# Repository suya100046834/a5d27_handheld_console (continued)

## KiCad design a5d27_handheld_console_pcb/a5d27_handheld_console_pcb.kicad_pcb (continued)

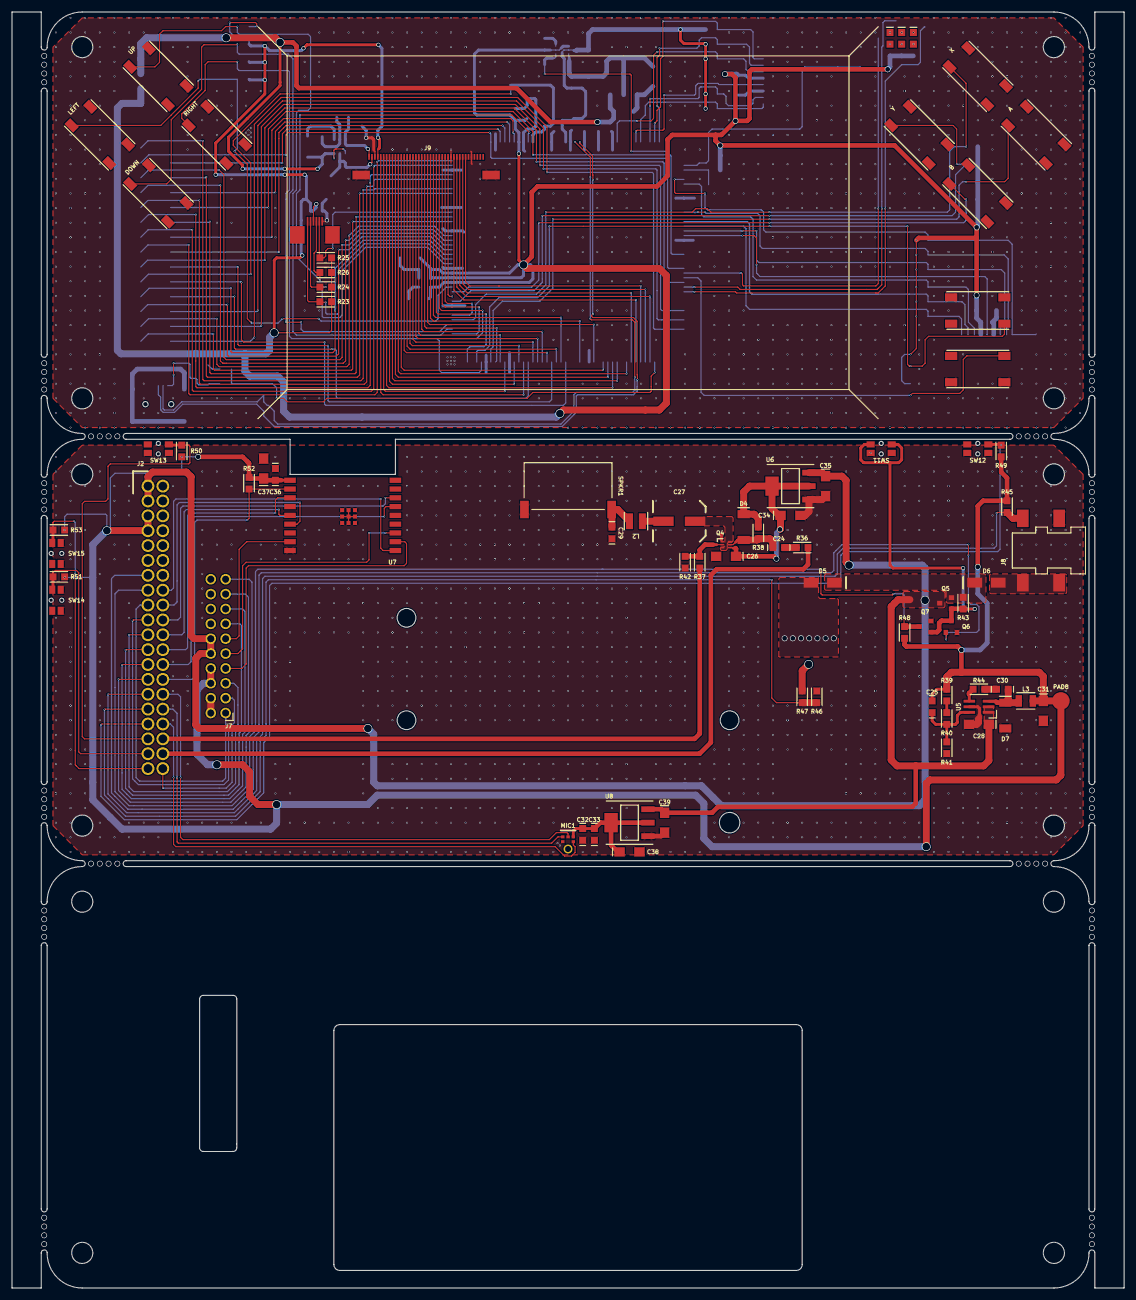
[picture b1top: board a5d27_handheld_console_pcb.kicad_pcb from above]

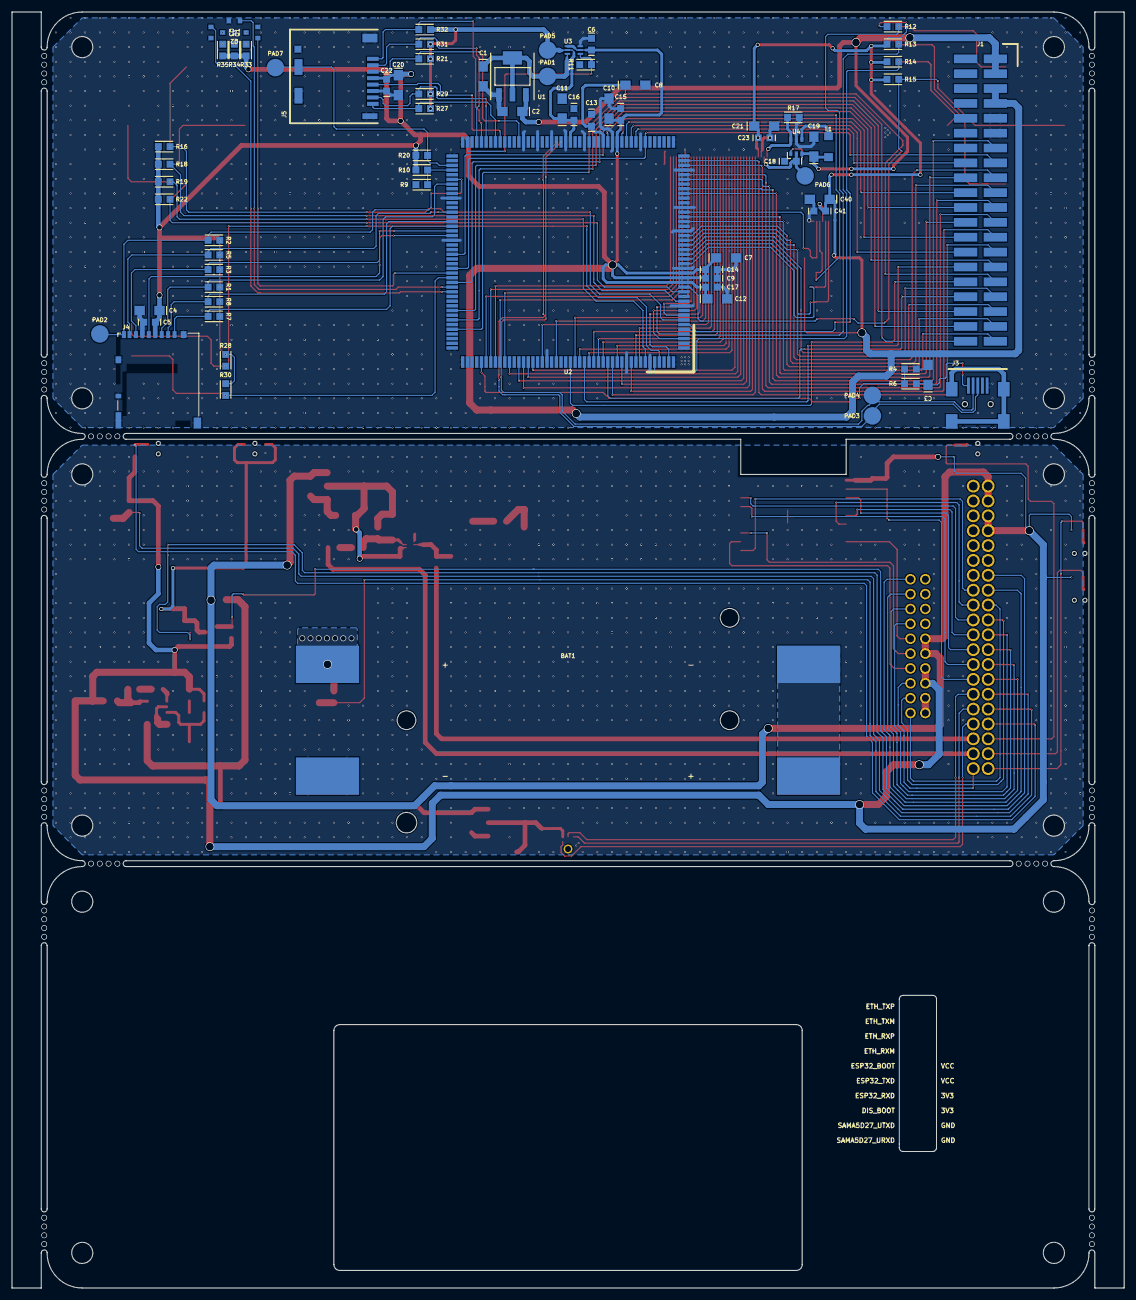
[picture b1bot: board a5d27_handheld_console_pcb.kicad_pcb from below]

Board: 2 copper layers, 190.0 x 218.0 mm, 153 parts (76 on the bottom side), 158 nets.

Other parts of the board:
A: A; SWITCH
B: B; SWITCH
DOWN: DOWN; SWITCH
LEFT: LEFT; SWITCH
RIGHT: RIGHT; SWITCH
UP: UP; SWITCH
X: X; SWITCH
Y: Y; SWITCH

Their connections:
/1_BOARD/BTN_1: UP.2; also elsewhere on the board
/1_BOARD/BTN_2: DOWN.2; also elsewhere on the board
/1_BOARD/BTN_3: RIGHT.2; also elsewhere on the board
/1_BOARD/BTN_4: LEFT.2; also elsewhere on the board
/1_BOARD/BTN_5: X.2; also elsewhere on the board
/1_BOARD/BTN_6: Y.2; also elsewhere on the board
/1_BOARD/BTN_7: A.2; also elsewhere on the board
/1_BOARD/BTN_8: B.2; also elsewhere on the board
GND_1: A.3, A.4, B.3, B.4, DOWN.3, DOWN.4, LEFT.3, LEFT.4, RIGHT.3, RIGHT.4, UP.3, UP.4, X.3, X.4, Y.3, Y.4; also elsewhere on the board

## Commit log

2024-01-07 first init
2024-01-07 Create linux
2024-01-09 Update sama5d27_handheld_defconfig
